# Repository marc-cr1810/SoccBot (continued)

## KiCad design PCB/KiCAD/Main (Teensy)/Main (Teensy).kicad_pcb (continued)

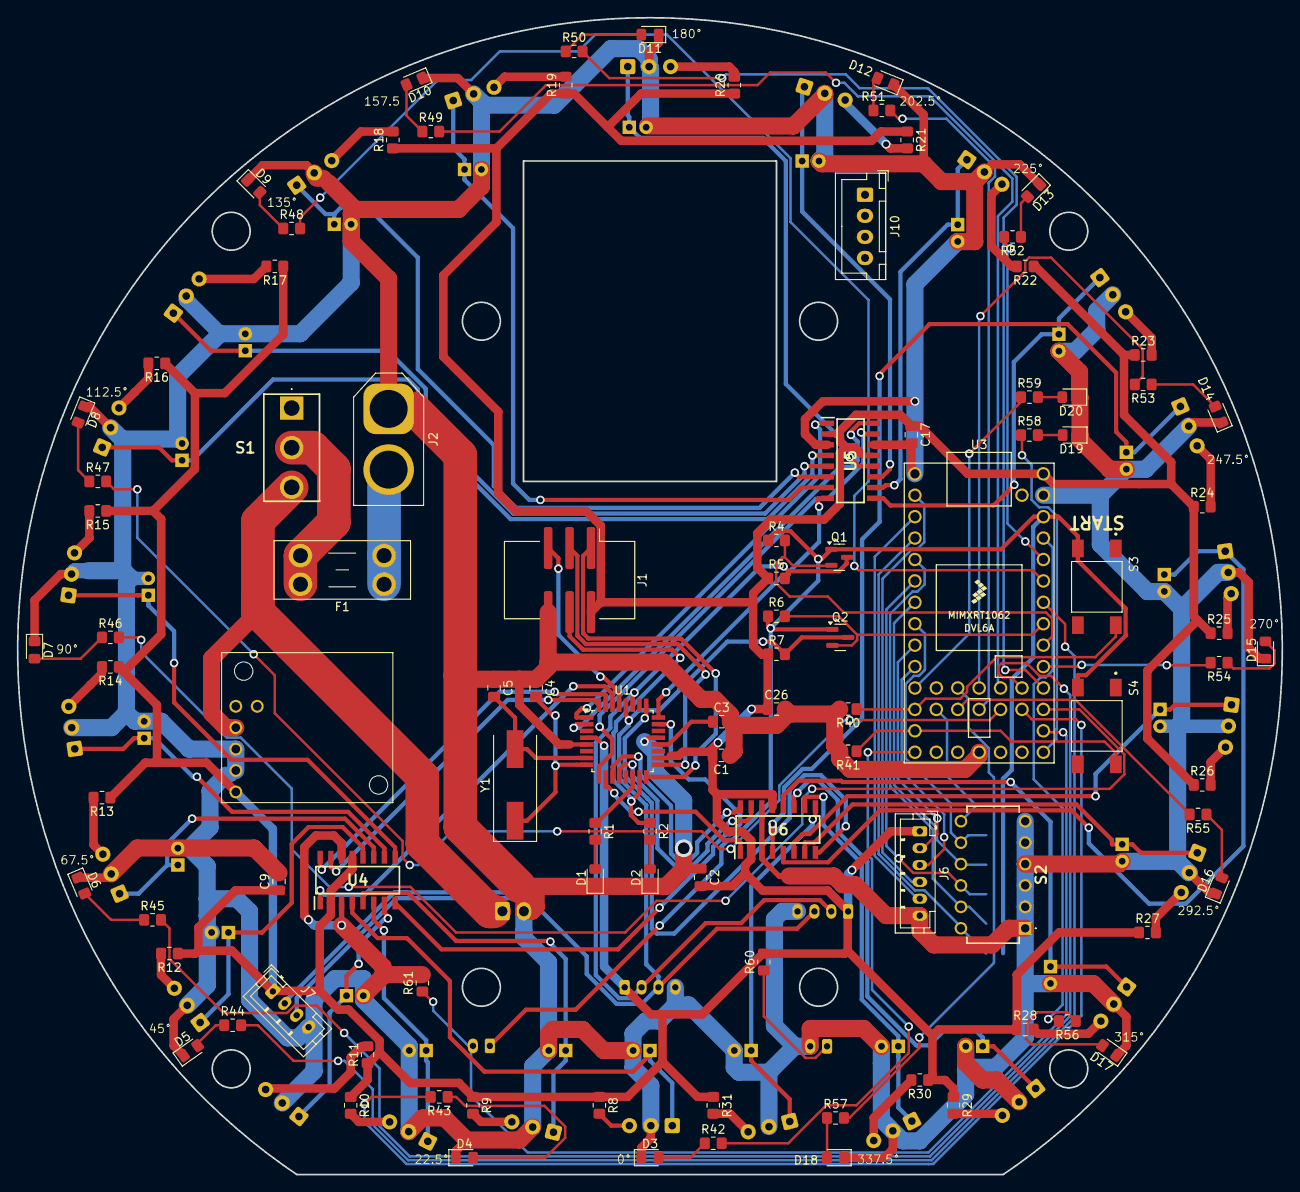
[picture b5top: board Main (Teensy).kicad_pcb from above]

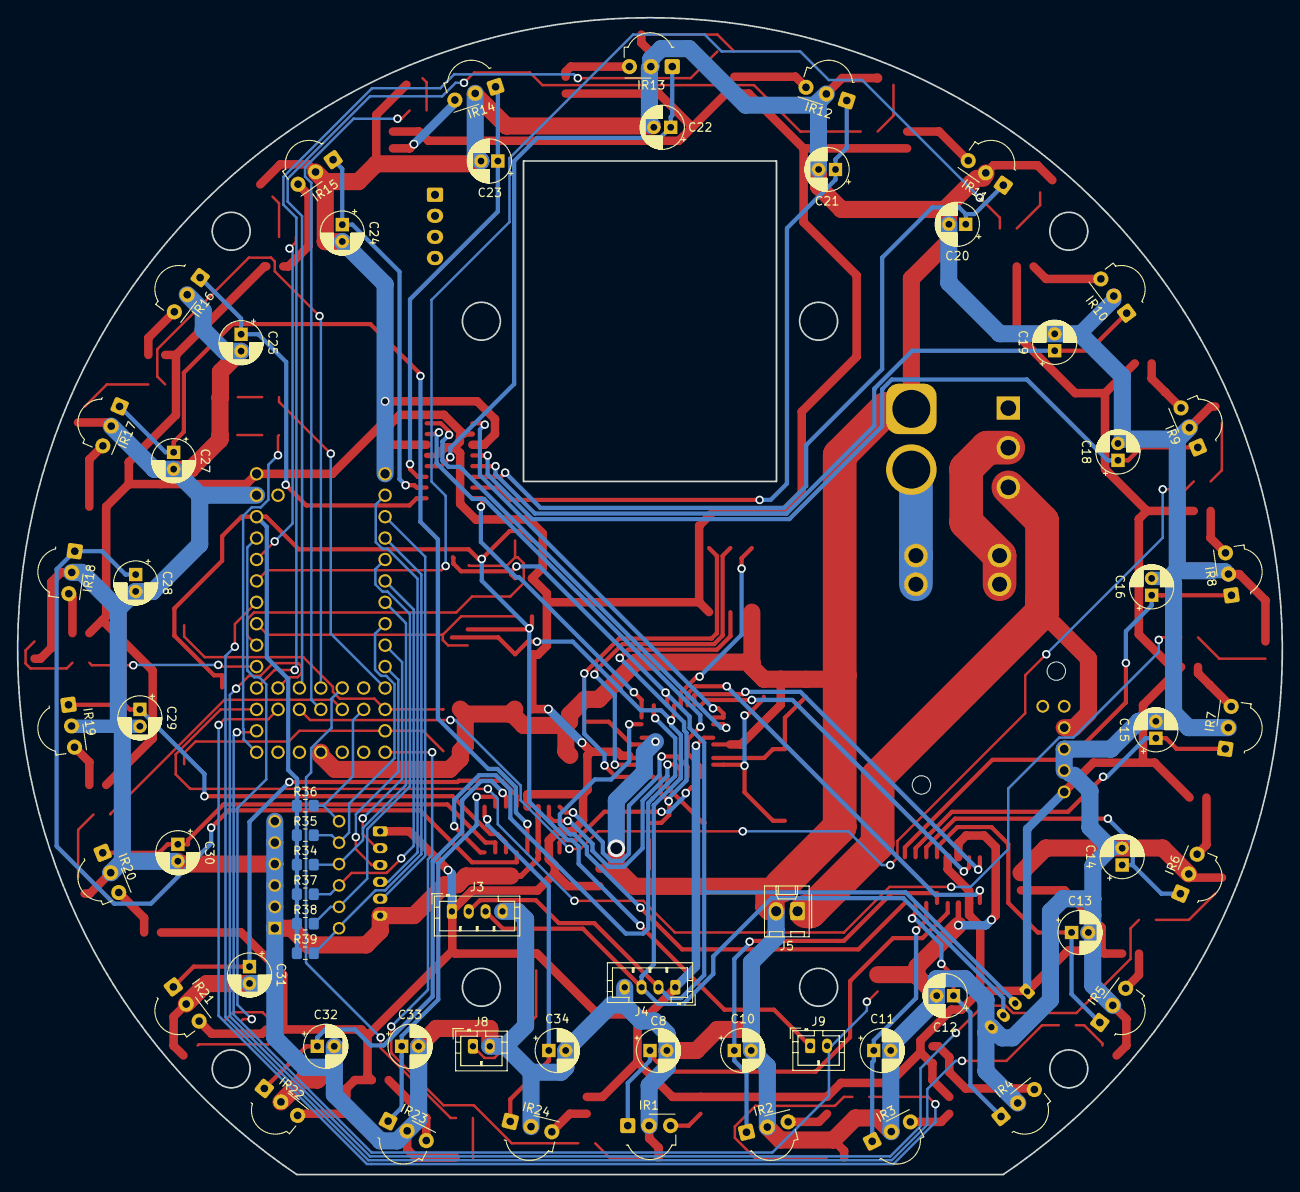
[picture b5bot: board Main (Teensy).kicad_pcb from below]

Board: 2 copper layers, 150.0 x 137.2 mm, 158 parts (59 on the bottom side), 130 nets.

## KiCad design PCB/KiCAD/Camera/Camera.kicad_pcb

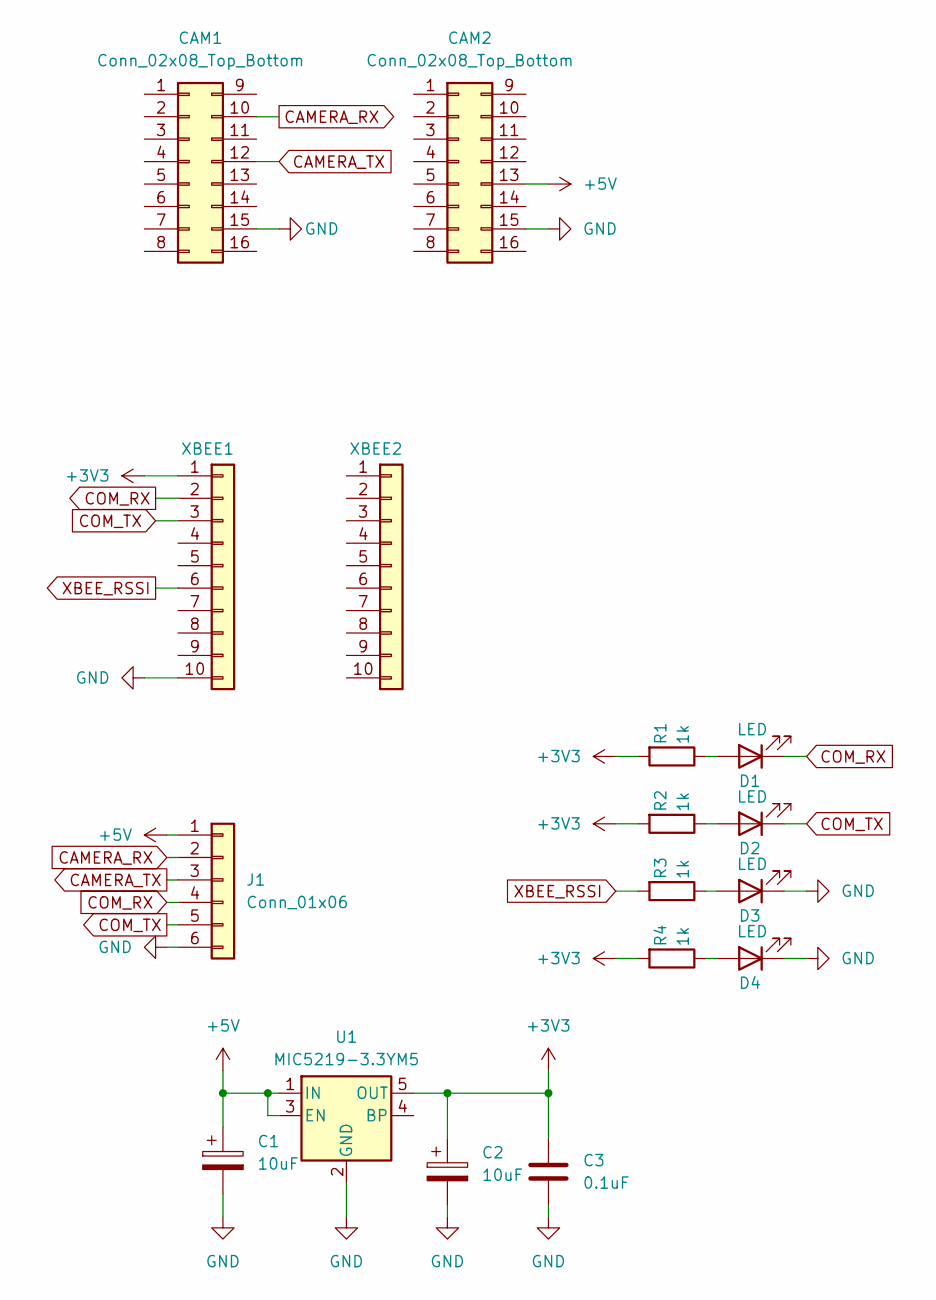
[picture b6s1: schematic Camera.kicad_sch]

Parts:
C1, C2: 10uF; CP_EIA-3216-12_Kemet-S_Pad1.58x1.35mm_HandSolder
C3: 0.1uF; C_0805_2012Metric_Pad1.18x1.45mm_HandSolder
CAM1, CAM2: Conn_02x08_Top_Bottom; PinSocket_2x08_P2.54mm_Vertical
D1, D2, D3, D4: LED; LED_0805_2012Metric_Pad1.15x1.40mm_HandSolder
J1: Conn_01x06; JST_PH_B6B-PH-K_1x06_P2.00mm_Vertical
R1, R2, R3, R4: 1k; R_0805_2012Metric_Pad1.20x1.40mm_HandSolder
U1: MIC5219-3.3YM5; SOT-23-5
XBEE1, XBEE2: Conn_01x10; PinSocket_1x10_P2.00mm_Vertical

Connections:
+3V3: C2.1, C3.1, R1.2, R2.2, R4.2, U1.5 (OUT), XBEE1.1
+5V: C1.1, CAM2.13, J1.1, U1.1 (IN), U1.3 (EN)
CAMERA_RX: CAM1.10, J1.2
CAMERA_TX: CAM1.12, J1.3
COM_RX: D1.1 (K), J1.4, XBEE1.2
COM_TX: D2.1 (K), J1.5, XBEE1.3
GND: C1.2, C2.2, C3.2, CAM1.15, CAM2.15, D3.1 (K), D4.1 (K), J1.6, U1.2 (GND), XBEE1.10
unnamed: D1.2 (A), R1.1
unnamed: D2.2 (A), R2.1
unnamed: D3.2 (A), R3.1
unnamed: D4.2 (A), R4.1
XBEE_RSSI: R3.2, XBEE1.6

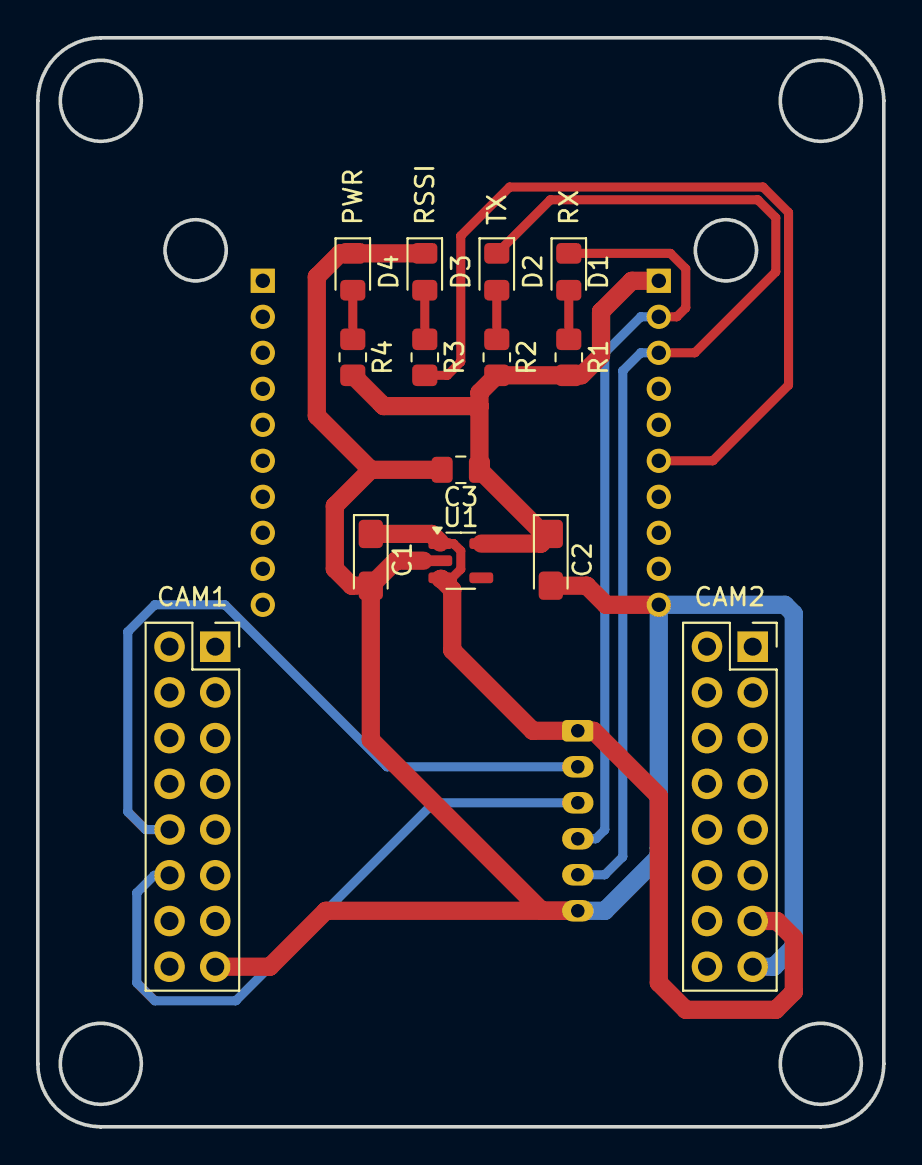
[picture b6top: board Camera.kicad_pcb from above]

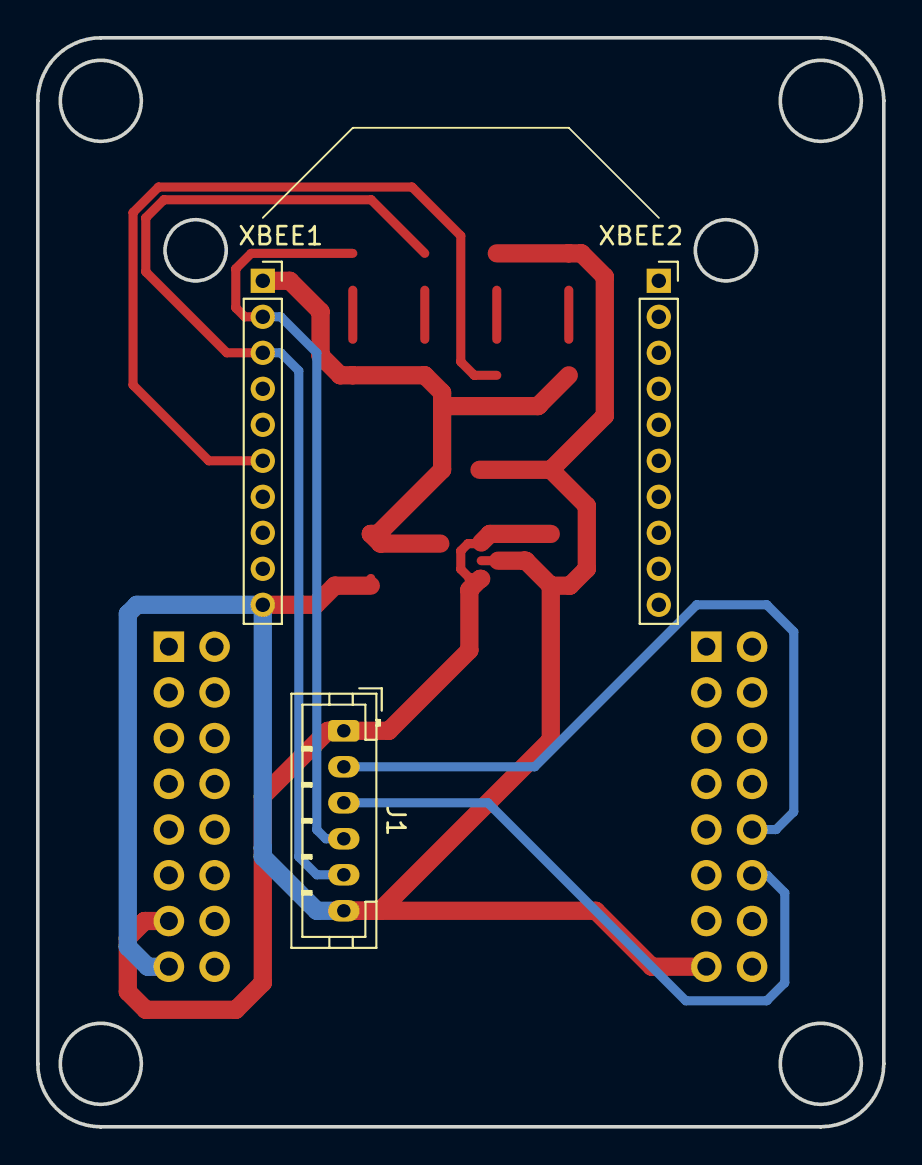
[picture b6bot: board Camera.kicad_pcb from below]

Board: 2 copper layers, 47.0 x 60.5 mm, 17 parts (3 on the bottom side), 12 nets.

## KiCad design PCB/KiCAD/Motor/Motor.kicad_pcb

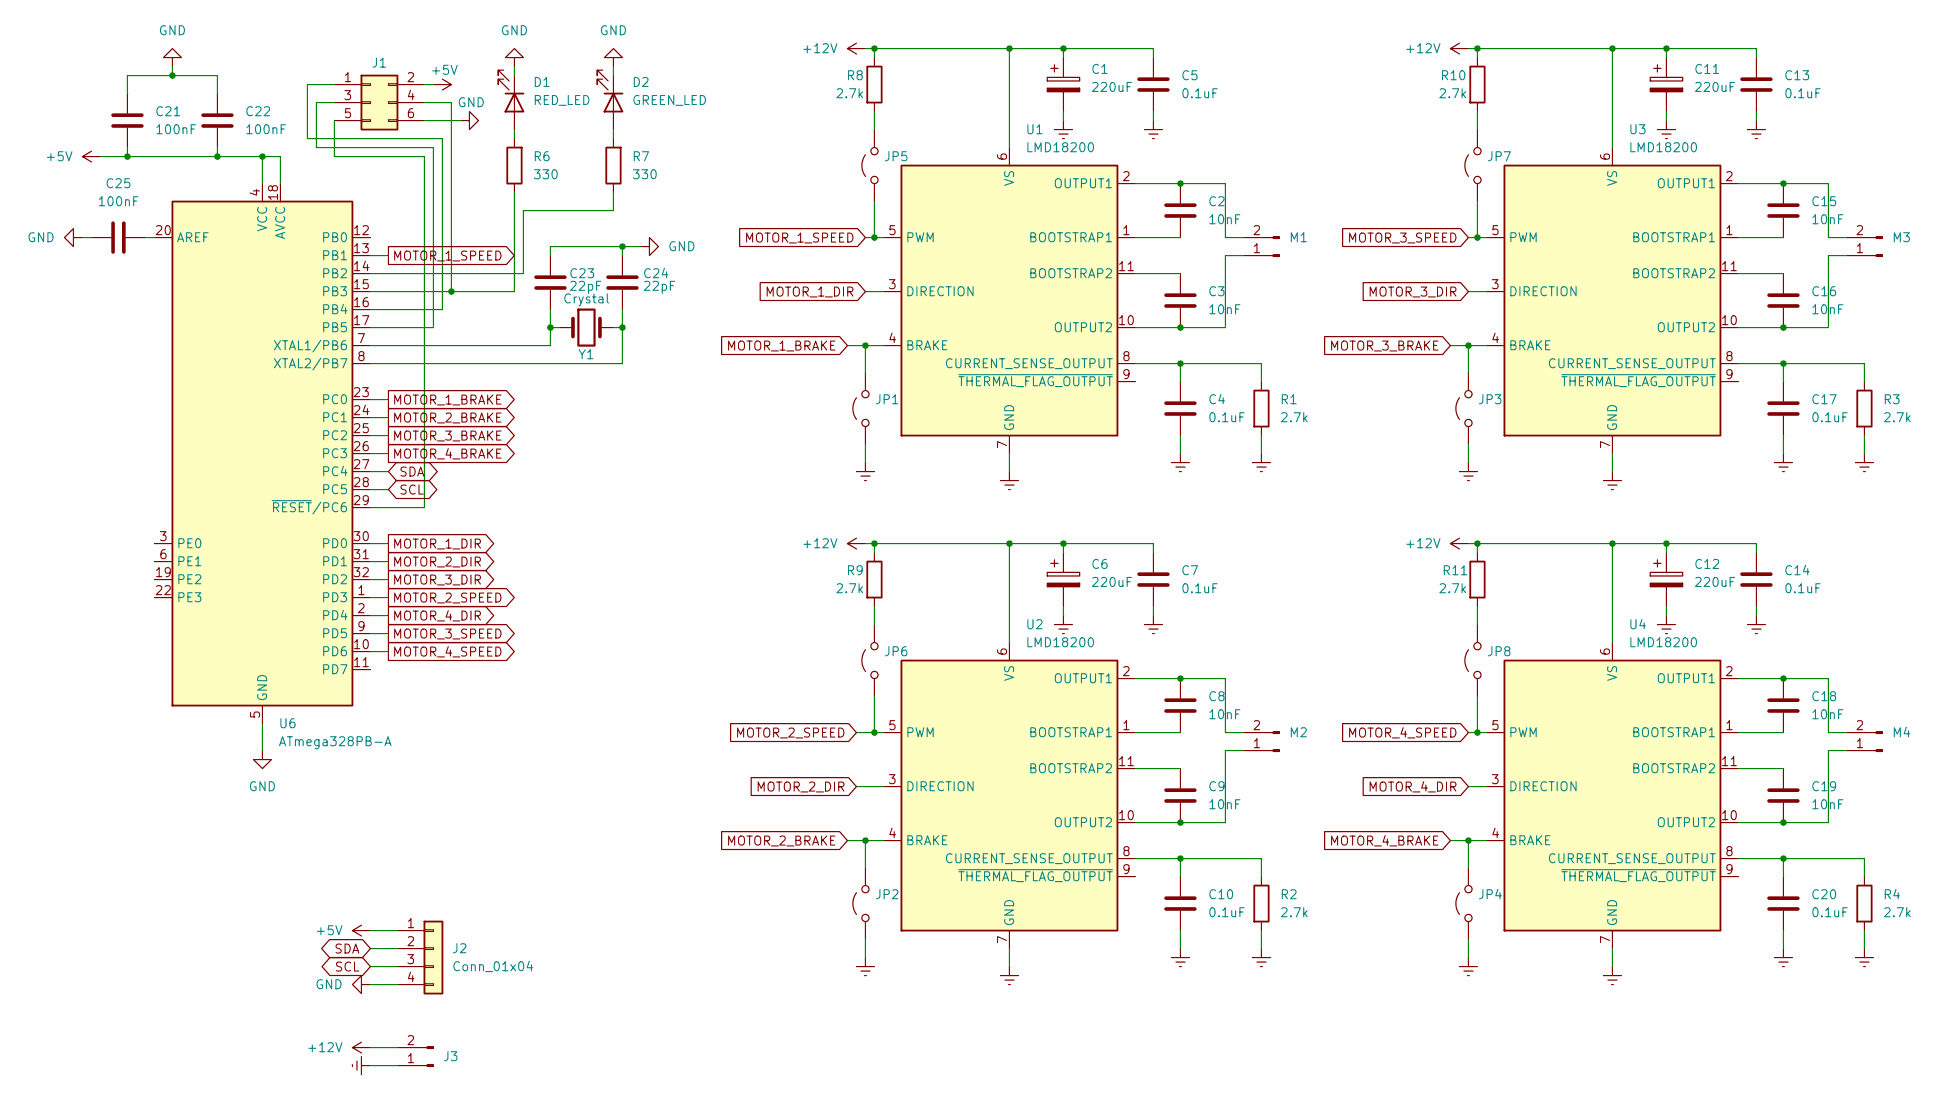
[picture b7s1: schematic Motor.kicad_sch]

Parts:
C1, C6, C11, C12: 220uF; CP_Elec_10x10
C2, C3, C8, C9, C15, C16, C18, C19: 10nF; C_1210_3225Metric_Pad1.33x2.70mm_HandSolder
C4, C5, C7, C10, C13, C14, C17, C20: 0.1uF; C_0805_2012Metric_Pad1.18x1.45mm_HandSolder
C21, C22, C25: 100nF; C_0805_2012Metric_Pad1.18x1.45mm_HandSolder
C23, C24: 22pF; C_0805_2012Metric_Pad1.18x1.45mm_HandSolder
D1: RED_LED; LED_0805_2012Metric_Pad1.15x1.40mm_HandSolder
D2: GREEN_LED; LED_0805_2012Metric_Pad1.15x1.40mm_HandSolder
J1: Conn_02x03_Odd_Even; IDC-Header_2x03_P2.54mm_Vertical_SMD
J2: Conn_01x04; JST_PH_B4B-PH-K_1x04_P2.00mm_Vertical
J3: Conn_01x02_Pin; Molex_KK-254_AE-6410-02A_1x02_P2.54mm_Vertical
JP1, JP2, JP3, JP4, JP5, JP6, JP7, JP8: Jumper_2_Open; TestPoint_2Pads_Pitch2.54mm_Drill0.8mm
M1, M2, M3, M4: Conn_01x02_Pin; Molex_KK-254_AE-6410-02A_1x02_P2.54mm_Vertical
R1, R2, R3, R4, R8, R9, R10, R11: 2.7k; R_0805_2012Metric_Pad1.20x1.40mm_HandSolder
R6, R7: 330; R_0805_2012Metric_Pad1.20x1.40mm_HandSolder
U1, U2, U3, U4: LMD18200; TO-220-11_P3.4x5.08mm_StaggerOdd_Lead4.85mm_Vertical
U6: ATmega328PB-A; TQFP-32_7x7mm_P0.8mm
Y1: Crystal; Crystal_SMD_HC49-SD

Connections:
+5V: C21.2, C22.2, J1.2, J2.1, U6.4 (VCC), U6.18 (AVCC)
+12V: C1.1, C5.1, C6.1, C7.1, C11.1, C12.1, C13.1, C14.1, J3.2, R8.1, R9.1, R10.1, R11.1, U1.6 (VS), U2.6 (VS), U3.6 (VS), U4.6 (VS)
Earth: C1.2, C4.2, C5.2, C6.2, C7.2, C10.2, C11.2, C12.2, C13.2, C14.2, C17.2, C20.2, J3.1, JP1.1 (A), JP2.1 (A), JP3.1 (A), JP4.1 (A), R1.2, R2.2, R3.2, R4.2, U1.7 (GND), U2.7 (GND), U3.7 (GND), U4.7 (GND)
GND: C21.1, C22.1, C23.1, C24.1, C25.2, D1.1 (K), D2.1 (K), J1.6, J2.4, U6.5 (GND), U6.21 (GND)
MOTOR_1_BRAKE: JP1.2 (B), U1.4 (BRAKE), U6.23 (PC0)
MOTOR_1_DIR: U1.3 (DIRECTION), U6.30 (PD0)
MOTOR_1_SPEED: JP5.1 (A), U1.5 (PWM), U6.13 (PB1)
MOTOR_2_BRAKE: JP2.2 (B), U2.4 (BRAKE), U6.24 (PC1)
MOTOR_2_DIR: U2.3 (DIRECTION), U6.31 (PD1)
MOTOR_2_SPEED: JP6.1 (A), U2.5 (PWM), U6.1 (PD3)
MOTOR_3_BRAKE: JP3.2 (B), U3.4 (BRAKE), U6.25 (PC2)
MOTOR_3_DIR: U3.3 (DIRECTION), U6.32 (PD2)
MOTOR_3_SPEED: JP7.1 (A), U3.5 (PWM), U6.9 (PD5)
MOTOR_4_BRAKE: JP4.2 (B), U4.4 (BRAKE), U6.26 (PC3)
MOTOR_4_DIR: U4.3 (DIRECTION), U6.2 (PD4)
MOTOR_4_SPEED: JP8.1 (A), U4.5 (PWM), U6.10 (PD6)
unnamed: D1.2 (A), R6.2
unnamed: D2.2 (A), R7.2
unnamed: J1.1, U6.16 (PB4)
unnamed: J1.3, U6.17 (PB5)
unnamed: J1.4, R6.1, U6.15 (PB3)
unnamed: J1.5, U6.29 (~RESET/PC6)
unnamed: JP5.2 (B), R8.2
unnamed: JP6.2 (B), R9.2
unnamed: JP7.2 (B), R10.2
unnamed: JP8.2 (B), R11.2
unnamed: C3.2, M1.1, U1.10 (OUTPUT2)
unnamed: C2.1, M1.2, U1.2 (OUTPUT1)
unnamed: C9.2, M2.1, U2.10 (OUTPUT2)
unnamed: C8.1, M2.2, U2.2 (OUTPUT1)
unnamed: C16.2, M3.1, U3.10 (OUTPUT2)
unnamed: C15.1, M3.2, U3.2 (OUTPUT1)
unnamed: C19.2, M4.1, U4.10 (OUTPUT2)
unnamed: C18.1, M4.2, U4.2 (OUTPUT1)
unnamed: C2.2, U1.1 (BOOTSTRAP1)
unnamed: C3.1, U1.11 (BOOTSTRAP2)
unnamed: C4.1, R1.1, U1.8 (CURRENT_SENSE_OUTPUT)
unnamed: C8.2, U2.1 (BOOTSTRAP1)
unnamed: C9.1, U2.11 (BOOTSTRAP2)
unnamed: C10.1, R2.1, U2.8 (CURRENT_SENSE_OUTPUT)
unnamed: C15.2, U3.1 (BOOTSTRAP1)
unnamed: C16.1, U3.11 (BOOTSTRAP2)
unnamed: C17.1, R3.1, U3.8 (CURRENT_SENSE_OUTPUT)
unnamed: C18.2, U4.1 (BOOTSTRAP1)
unnamed: C19.1, U4.11 (BOOTSTRAP2)
unnamed: C20.1, R4.1, U4.8 (CURRENT_SENSE_OUTPUT)
unnamed: C25.1, U6.20 (AREF)
unnamed: R7.1, U6.14 (PB2)
unnamed: C23.2, U6.7 (XTAL1/PB6), Y1.1
unnamed: C24.2, U6.8 (XTAL2/PB7), Y1.2
SCL: J2.3, U6.28 (PC5)
SDA: J2.2, U6.27 (PC4)

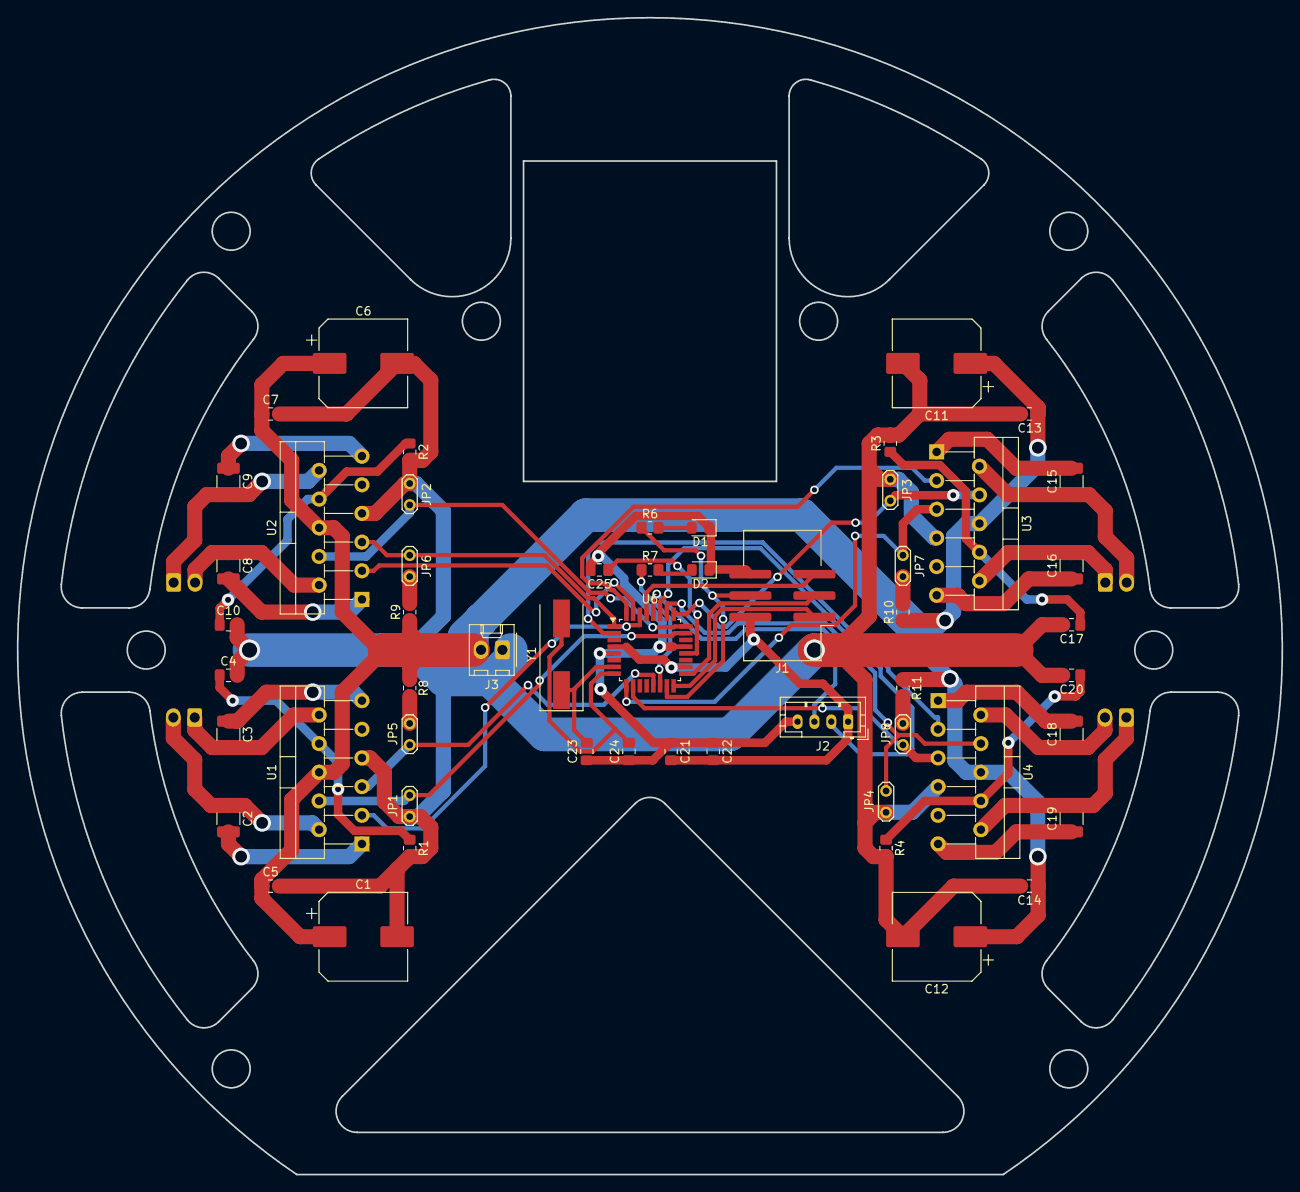
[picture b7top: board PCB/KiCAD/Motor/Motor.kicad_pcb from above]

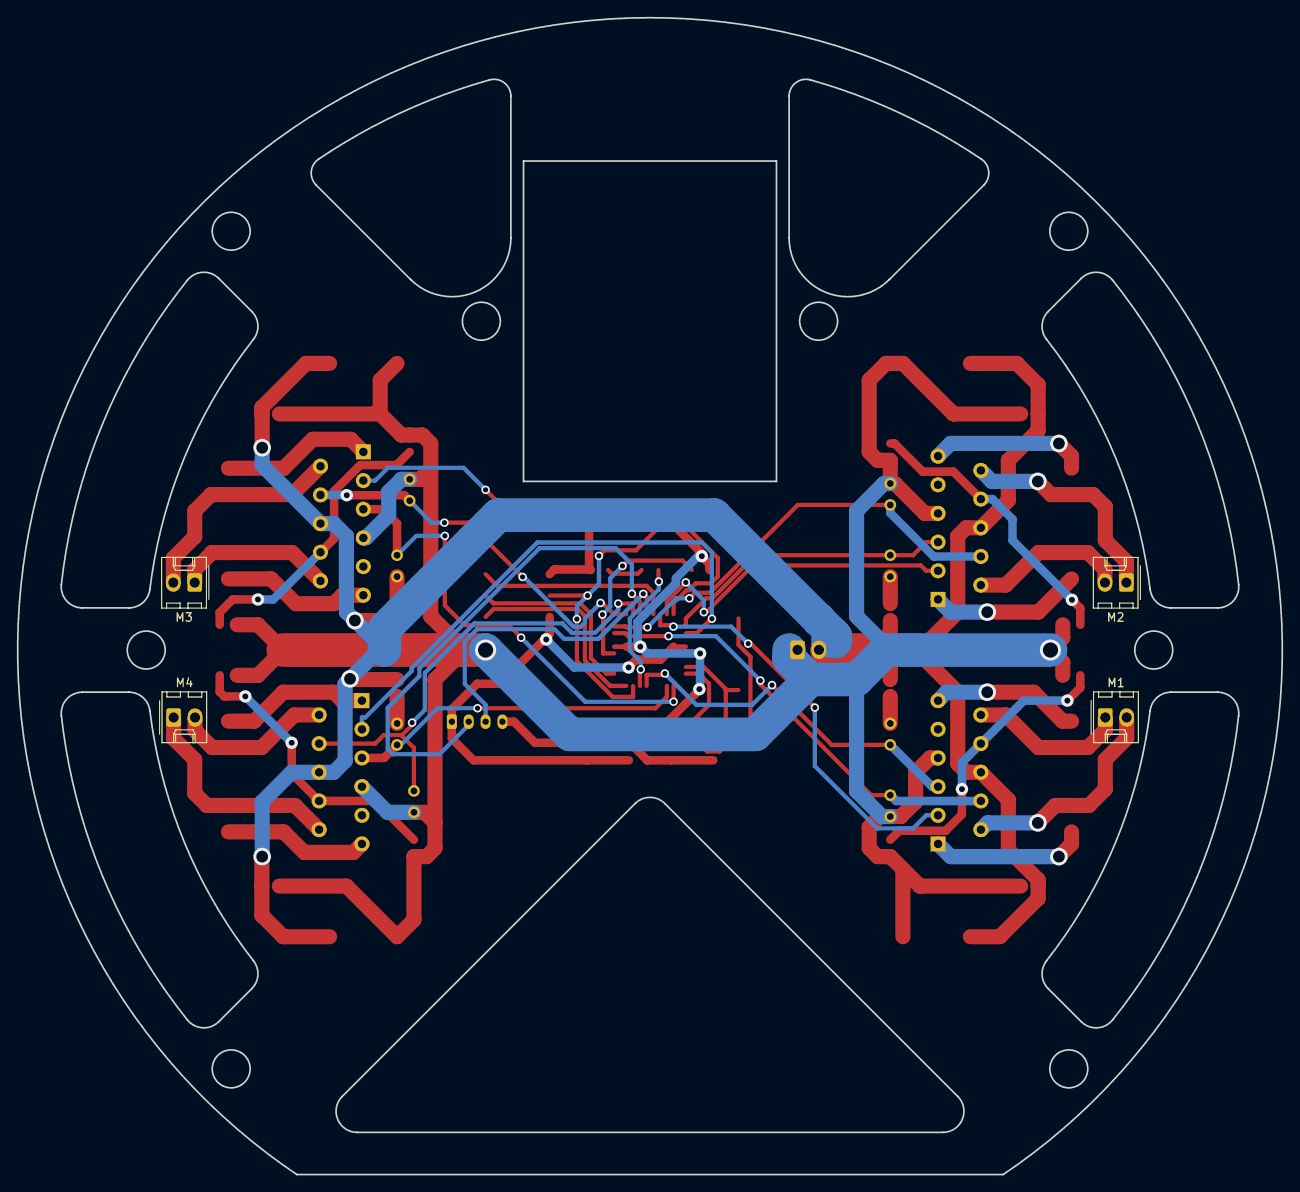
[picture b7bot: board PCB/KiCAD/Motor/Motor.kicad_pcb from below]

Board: 2 copper layers, 150.0 x 137.2 mm, 58 parts (4 on the bottom side), 52 nets.

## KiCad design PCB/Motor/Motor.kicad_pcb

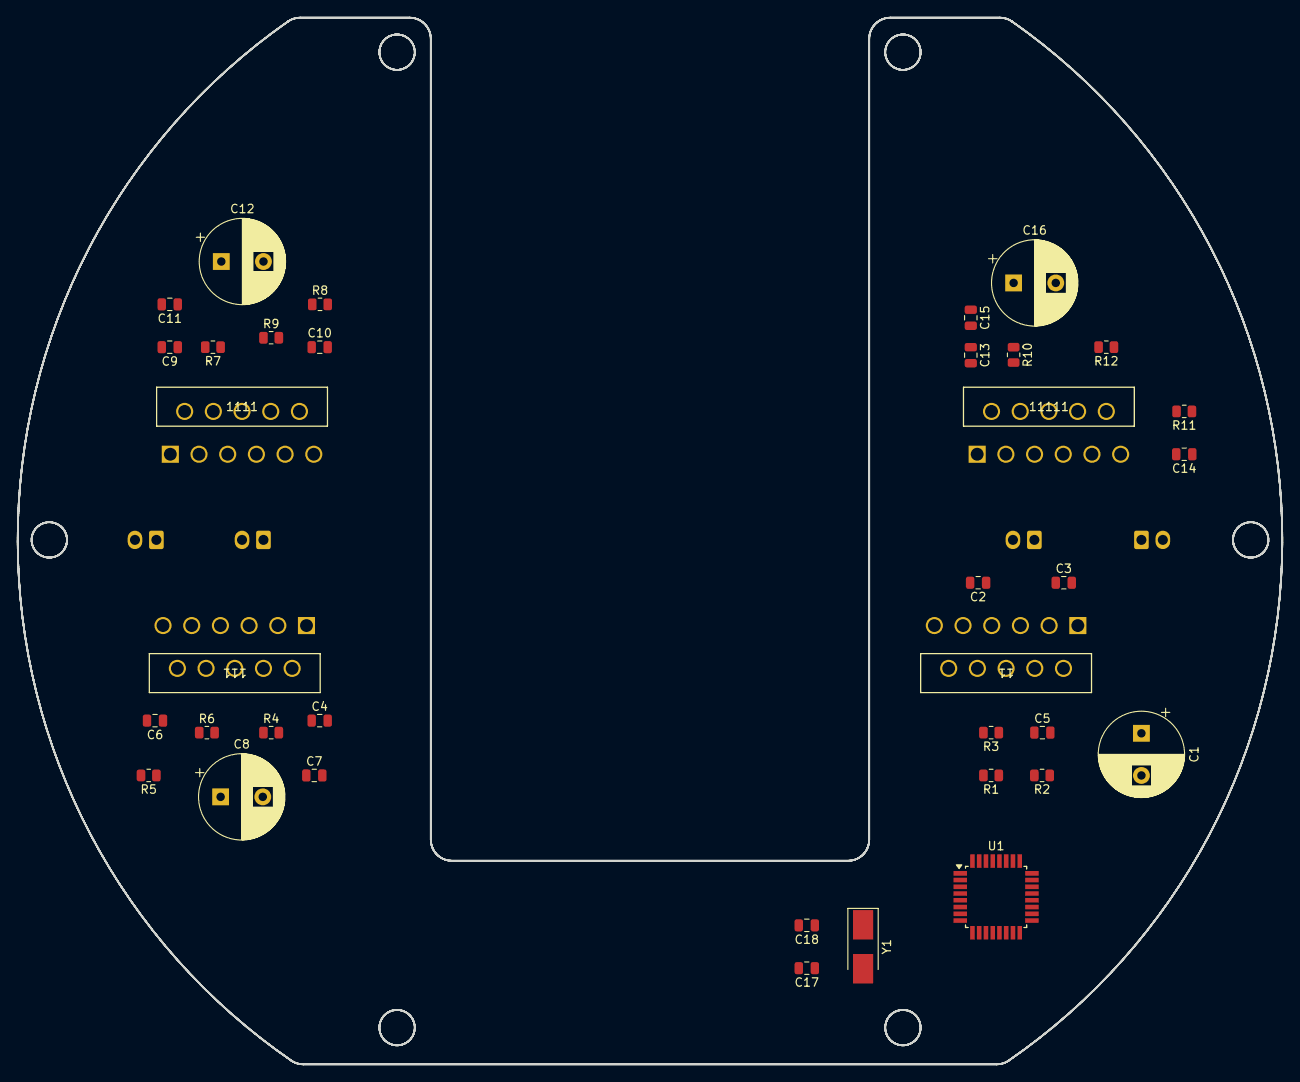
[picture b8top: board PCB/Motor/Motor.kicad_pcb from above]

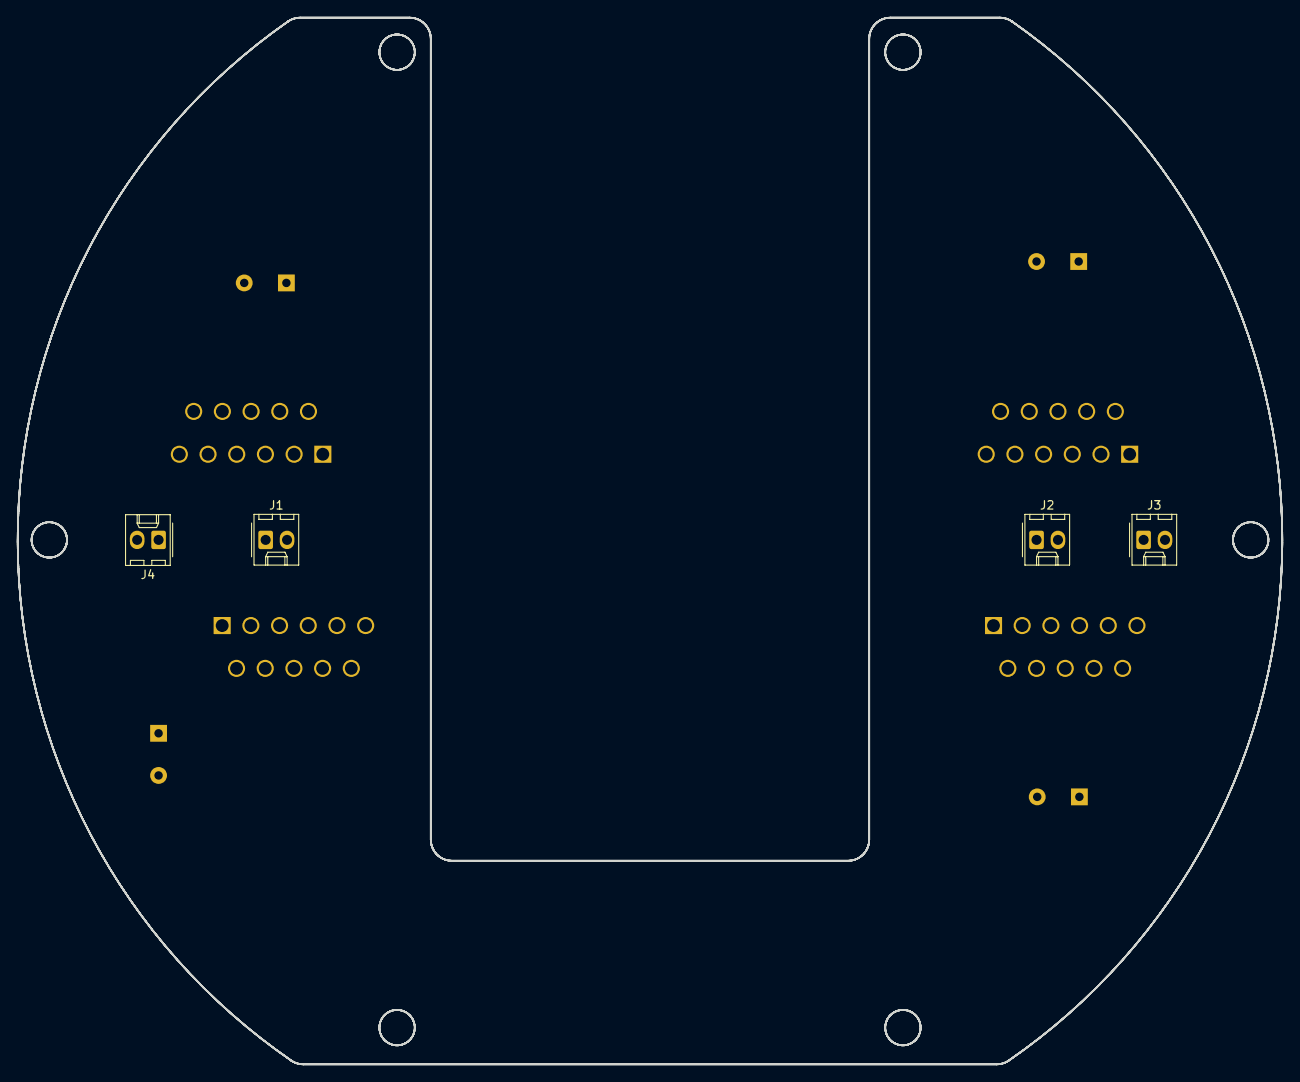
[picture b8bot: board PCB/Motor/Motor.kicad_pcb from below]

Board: 2 copper layers, 150.0 x 124.1 mm, 40 parts (4 on the bottom side), 26 nets, no tracks yet.

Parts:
11, 111, 1111, 11111: LMD18200T/LF14; TA11B
C1, C8, C12, C16: 1200uF; CP_Radial_D10.0mm_P5.00mm
C2, C3, C4, C6, C9, C10, C13, C14: 10nF; C_0805_2012Metric
C5, C7, C11, C15: 1uF; C_0805_2012Metric
C17, C18: 22pF; C_0805_2012Metric
J1: M1; Molex_KK-254_AE-6410-02A_1x02_P2.54mm_Vertical
J2: M2; Molex_KK-254_AE-6410-02A_1x02_P2.54mm_Vertical
J3: M3; Molex_KK-254_AE-6410-02A_1x02_P2.54mm_Vertical
J4: M4; Molex_KK-254_AE-6410-02A_1x02_P2.54mm_Vertical
R1, R2, R4, R5, R7, R8, R10, R11: 12; R_0805_2012Metric
R3, R6, R9, R12: 2.7k; R_0805_2012Metric
U1: ATmega328P-A; TQFP-32_7x7mm_P0.8mm
Y1: Crystal; Crystal_SMD_5032-2Pin_5.0x3.2mm_HandSoldering

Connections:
+12V: 11.6 (VS), 111.6 (VS), 1111.6 (VS), 11111.6 (VS), C1.1, C5.2, C7.2, C8.1, C11.2, C12.1, C15.2, C16.1, R2.1, R4.1, R7.1, R10.1
Earth: 11.7 (GND), 111.7 (GND), 1111.7 (GND), 11111.7 (GND), C1.2, C5.1, C7.1, C8.2, C11.1, C12.2, C15.1, C16.2, C17.2, C18.2, R1.1, R3.1, R5.1, R6.1, R8.1, R9.1, R11.1, R12.1
unnamed: 11.1 (BS_1), C3.2
unnamed: 11.11 (BS_2), C2.2
unnamed: 11.8 (I_SEN), R3.2
unnamed: 11.2 (OUT_1), C3.1, J1.1, R2.2
unnamed: 11.10 (OUT_2), C2.1, J1.2, R1.2
unnamed: 111.1 (BS_1), C4.2
unnamed: 111.11 (BS_2), C6.2
unnamed: 111.8 (I_SEN), R6.2
unnamed: 111.2 (OUT_1), C4.1, J2.1, R4.2
unnamed: 111.10 (OUT_2), C6.1, J2.2, R5.2
unnamed: 1111.1 (BS_1), C9.2
unnamed: 1111.11 (BS_2), C10.2
unnamed: 1111.8 (I_SEN), R9.2
unnamed: 1111.2 (OUT_1), C9.1, J3.1, R7.2
unnamed: 1111.10 (OUT_2), C10.1, J3.2, R8.2
unnamed: 11111.1 (BS_1), C13.2
unnamed: 11111.11 (BS_2), C14.2
unnamed: 11111.8 (I_SEN), R12.2
unnamed: 11111.2 (OUT_1), C13.1, J4.1, R10.2
unnamed: 11111.10 (OUT_2), C14.1, J4.2, R11.2
unnamed: U1.3 (GND), U1.5 (GND), U1.21 (GND)
unnamed: U1.4 (VCC), U1.6 (VCC)
unnamed: C18.1, U1.7 (XTAL1/PB6), Y1.1
unnamed: C17.1, U1.8 (XTAL2/PB7), Y1.2

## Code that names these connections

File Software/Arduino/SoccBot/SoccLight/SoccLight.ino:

#include <Wire.h>
#include <robot.h>

#include "light_cluster.h"

#define THRESHOLD	800

robot_state_t state(11, 10);

analog_multi_t light_cluster_1(PIN_PC0, PIN_PD0, PIN_PD1, PIN_PD2);
analog_multi_t light_cluster_2(PIN_PC1, PIN_PD3, PIN_PD4, PIN_PD5);
analog_multi_t light_cluster_3(PIN_PC2, PIN_PD6, PIN_PD7, PIN_PB0);

light_cluster_t light_clusters[LIGHT_SENSOR_COUNT - 1];

bool on_white = false;
uint16_t angle = 0;
uint32_t lightsensors = 0;

void setup()
{
	state.set_state(robot_state_t::booted);

	Wire.begin(LIGHT_I2C_ADDRESS);
	Wire.onRequest(i2c_request_event);
	Wire.onReceive(i2c_recieve_event);

	delay(100);
	state.set_state(robot_state_t::standby);
}

uint16_t read_light_sensor(uint8_t index)
{
	uint8_t cluster_index = floor((float)index / 8.0f);
	analog_multi_t* cluster = nullptr;
	switch (cluster_index)
	{
	case 0: cluster = &light_cluster_1; break;
	case 1: cluster = &light_cluster_2; break;
	case 2: cluster = &light_cluster_3; break;
	default: state.set_state(robot_state_t::error); return 0;
	}

	uint8_t cluster_light_index = index - (cluster_index * 8);
	if (cluster_light_index > 0b111)
	{
		state.set_state(robot_state_t::error);
		return 0;
	}
	return cluster->read(cluster_light_index);
}

void loop()
{
	state.update();

	int count = 0;
	int8_t min = -1;
	int8_t max = -1;
	uint32_t values = 0;
	bool is_cluster = false;

	for (ssize_t i = 0; i < LIGHT_SENSOR_COUNT; i++)
	{
		bool value = read_light_sensor(i) > THRESHOLD;
		values |= (uint32_t)(value ? 1 : 0) << (23 - i);

		if (is_cluster)
		{
			if (!value)
			{
				max = i - 1;
				light_clusters[count].set_min(min);
				light_clusters[count].set_max(max);
				count++;
				min = -1;
				max = -1;
				is_cluster = false;
			}
			else if (i == (LIGHT_SENSOR_COUNT - 1))
			{
				max = i;
				if (count > 0 && light_clusters[0].get_min() == 0)
				{
					light_clusters[0].set_min(max);
					min = -1;
					max = -1;
					is_cluster = false;
				}
				else
				{
					max = i - 1;
					light_clusters[count].set_min(min);
					light_clusters[count].set_max(max);
					count++;
					min = -1;
					max = -1;
					is_cluster = false;
				}
			}
		}
		else if (value)
		{
			min = i;
			is_cluster = true;
		}
	}

	if (count > 0)
	{
		light_cluster_t& cluster = light_clusters[0];
		for (int i = 1; i < count; i++)
		{
			if (light_clusters[i].count() > cluster.count())
			{
				cluster = light_clusters[i];
			}
		}
		angle = round(cluster.angle() * 100);
	}
	else
	{
		angle = 0;
	}
	lightsensors = values;
	on_white = count > 0;
}

void i2c_request_event()
{
	Wire.write((uint8_t)((angle >> 8) & 0xFF));
	Wire.write((uint8_t)(angle & 0xFF));
	Wire.write((uint8_t)on_white);
	Wire.write((uint8_t)(lightsensors >> 16) & 0xFF);
	Wire.write((uint8_t)(lightsensors >> 8) & 0xFF);
	Wire.write((uint8_t)lightsensors & 0xFF);
}

void i2c_recieve_event(int bytes)
{

}

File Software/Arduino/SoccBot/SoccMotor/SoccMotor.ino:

#include <Wire.h>
#include <robot.h>

#include "maths/vector2.h"
#include "maths/vector3.h"
#include "maths/vector4.h"
#include "maths/matrix_4x3.h"
#include "maths/matrix_3x4.h"
#include "maths/matrix_3x3.h"

struct motor_t
{
	uint8_t pin_speed;
	uint8_t pin_dir;
	uint8_t pin_brake;

	void setup()
	{
		pinMode(pin_speed, OUTPUT);
		pinMode(pin_dir, OUTPUT);
		pinMode(pin_brake, OUTPUT);

		analogWrite(pin_speed, 0);
		digitalWrite(pin_dir, LOW);
		digitalWrite(pin_brake, LOW);
	}

	void set_speed(int16_t speed)
	{
		uint16_t s = abs(speed) % 256;
		uint8_t dir = speed < 0 ? LOW : HIGH;

		analogWrite(pin_speed, s);
		digitalWrite(pin_dir, dir);
	}
};

motor_t motor_1 = { PIN_PB1, PIN_PD0, PIN_PC0 };
motor_t motor_2 = { PIN_PD3, PIN_PD1, PIN_PC1 };
motor_t motor_3 = { PIN_PD5, PIN_PD2, PIN_PC2 };
motor_t motor_4 = { PIN_PD6, PIN_PD4, PIN_PC3 };

#define MOTOR_ANGLE_1	45
#define MOTOR_ANGLE_2	135
#define MOTOR_ANGLE_3	225
#define MOTOR_ANGLE_4	315

const float motor_drive_angles[] = {
	((MOTOR_ANGLE_1 + 90) % 360) * DEG_TO_RAD,
	((MOTOR_ANGLE_2 + 90) % 360) * DEG_TO_RAD,
	((MOTOR_ANGLE_3 + 90) % 360) * DEG_TO_RAD,
	((MOTOR_ANGLE_4 + 90) % 360) * DEG_TO_RAD
};

void i2c_request_event();
void i2c_recieve_event(int bytes);
void move_motors(float direction, float rotation, int16_t speed);
void rotate_motors(int16_t speed);
void stop_motors();

robot_state_t state(11, 10);

matrix_4x3 mat_wheels;

void setup()
{
	state.set_state(robot_state_t::booted);

	Wire.begin(MOTOR_I2C_ADDRESS);
	Wire.onRequest(i2c_request_event);
	Wire.onReceive(i2c_recieve_event);

	motor_1.setup();
	motor_2.setup();
	motor_3.setup();
	motor_4.setup();

	matrix_type mat[3][4] = {
		{ cosf(motor_drive_angles[0]), cosf(motor_drive_angles[1]), cosf(motor_drive_angles[2]), cosf(motor_drive_angles[3]) },
		{ sinf(motor_drive_angles[0]), sinf(motor_drive_angles[1]), sinf(motor_drive_angles[2]), sinf(motor_drive_angles[3]) },
		{ 1, 1, 1, 1}
	};
	matrix_3x4 m(mat);
	matrix_4x3 m_t = matrix_3x4::transpose(m);
	matrix_3x3 mat3x3 = m_t * m;
	matrix_3x3 m_inv = matrix_3x3::inverse(mat3x3);
	auto m_near_final = m * m_inv;
	mat_wheels = matrix_3x4::transpose(m_near_final);

	state.set_state(robot_state_t::standby);
}

void loop()
{
	state.update();
}

void i2c_request_event()
{

}

void i2c_recieve_event(int bytes)
{
	uint8_t* buffer = new uint8_t[bytes];
	auto bytes_read = Wire.readBytes(buffer, bytes);

	if (bytes_read == 0)
	{
		delete[] buffer;
		return;
	}

	uint8_t cmd = buffer[0];
	switch (cmd)
	{
	case CMD_MOTOR_MOVE:
	{
		if (bytes_read < 7)
		{
			break;
		}

		int16_t direction = ((buffer[1] & 0xFF) << 8) | (buffer[2] & 0xFF);
		int16_t rotation = ((buffer[3] & 0xFF) << 8) | (buffer[4] & 0xFF);
		int16_t speed = ((buffer[5] & 0xFF) << 8) | (buffer[6] & 0xFF);

		move_motors((float)direction / 100.0f, (float)rotation / 100.0f, speed);
		break;
	}
	case CMD_MOTOR_ROTATE:
	{
		if (bytes_read < 3)
		{
			break;
		}

		int16_t speed = ((buffer[1] & 0xFF) << 8) | (buffer[2] & 0xFF);
		rotate_motors((float)speed);
		break;
	}
	case CMD_MOTOR_STOP:
	{
		stop_motors();
		break;
	}
	}

	delete[] buffer;
}

void move_motors(float direction, float rotation, int16_t speed)
{
	Vector2f dir(direction);
	vector3 vec_dir(dir.GetX(), dir.GetY(), rotation);
	auto motor_speeds = mat_wheels * vec_dir;

	motor_1.set_speed(motor_speeds[0] * speed);
	motor_2.set_speed(motor_speeds[1] * speed);
	motor_3.set_speed(motor_speeds[2] * speed);
	motor_4.set_speed(motor_speeds[3] * speed);
}

void rotate_motors(int16_t speed)
{
	motor_1.set_speed(speed);
	motor_2.set_speed(speed);
	motor_3.set_speed(speed);
	motor_4.set_speed(speed);
}

void stop_motors()
{
	motor_1.set_speed(0);
	motor_2.set_speed(0);
	motor_3.set_speed(0);
	motor_4.set_speed(0);
}

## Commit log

2024-06-22 Initial files
2024-06-25 Lower and upper plates, light sensor and motor PCBs, lower shroud and invalid sketch for upper shroud
2024-06-28 Upper shrould and PCB. Start to the motor mounts
2024-07-06 Prototype 1
2024-07-06 Fix for the Main PCB on prototype 1
2024-07-06 Shrank the sizes for the upper and lower plates, removed unnecessary screws
2024-07-14 Prototype V2
2024-08-15 Updated CAD design and PCB's
2024-08-15 New PCB and CAD designs
2024-08-25 Base library software code and some minor fixes to CAD designs
2024-08-25 Added missing *.vcxitems for Robot library
2024-08-25 Added LED array along with digital and analog multiplexer hardware
2024-08-26 Battery XT60 was reversed
2024-08-27 Added compatability for ATMEGA328PB chips and new projects
2024-08-29 I2C Communication
2024-08-29 Added TSSP angles
2024-09-04 IR sensor clusters and ball angle, basic light sensor * light sensor threshold needs tweaking
2024-10-09 Second design iteration
2024-10-09 Start of 3rd redesign
2025-03-26 Update CAD File
2025-03-26 Updates to Software
2025-03-29 Lost of work done to the design
2025-03-29 Creation of PCB files
2025-03-31 Start of PCBs
2025-04-01 Placed components on Lower PCB
2025-04-05 More work to the lower PCB
2025-04-05 Finished routing main motor controller connections and added connectors
2025-04-06 Added labels and fixed label positions
2025-04-06 Start to upper PCB
2025-04-10 More work to main PCB
2025-04-11 More work to the Main PCB and refinement of Via sizes
2025-08-21 Changes to the main PCB
2025-09-10 Updated to main PCB
2025-09-11 More PCB updates
2025-09-11 The Main PCB is now curved
2025-09-17 Changes to the bottom walls
2025-09-17 Redesign
2025-09-17 Start to the upper plate
2025-09-20 More work done to the new design
2025-09-20 VNH7070 board
2025-09-21 Added tolderance to the motor mounts
2025-09-21 New motor controllers for the main PCB
2025-09-21 Added a dribbler motor controller
2025-09-22 Updates to the CAD file
2025-09-22 Changed to PCB and CAD
2025-09-23 Added kicker and spare serial and i2c
2025-09-23 Added a handle
2025-09-23 Added a BNO055 and traced PCB (incomplete, no DRC pass)
2025-09-23 Finished traces and made them curved
2025-09-24 Redone main PCB traces and started lower PCB
2025-09-27 Work on the lower PCB
2025-09-27 Started aranging the LDRs and LEDs
2025-09-28 More chnages to LED positions and annotations
2025-09-28 Positioned LDRs and LEDs
2025-09-29 Cleaned up LDR and LED locations
2025-09-29 Started routing lower PCB
2025-09-30 Traced lower PCB (mostly)
2025-09-30 Lower PCb fully traced
2025-09-30 Uh oh there was a +5V rail
2025-10-02 Start of tracing again
2025-10-02 More trace optimizations
2025-10-03 More tweaks
2025-10-06 More tweaks to the lower PCB
2025-10-06 Added another switch
